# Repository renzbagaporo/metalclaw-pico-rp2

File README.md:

# MetalClaw Pico RP2

An RP2354B board for testing firmware on a Raspberry Pi Pico or Pico 2.
[Metalclaw firmware](https://github.com/renzbagaporo/metalclaw-fw) provides
Python-controlled peripheral emulation and a USB debug probe. The carrier
connects those functions to the target's GPIO, analogue inputs and SWD port.

- Emulate I2C, SPI and UART devices connected to the target.
- Generate and read digital signals on the target's exposed GPIOs.
- Supply filtered PWM stimulus to its three ADC inputs.
- Program and debug the target through SWD; control its reset and regulator enable.

## Hardware

| | |
| --- | --- |
| Controller | RP2354B with 2 MB in-package flash |
| PSRAM | 8 MB, APS6404L-3SQR-SN |
| USB | USB-C, full speed |
| Target interface | Pico / Pico 2 GPIO, power and SWD contacts; 3.3 V GPIO logic |
| Board | 21 × 51 mm, four layers, 1.6 mm, castellated edges |

## Pinout

The **Pico** columns name the target signals; the **RP2354B** columns show
the carrier GPIOs connected to them. The colored function labels belong to
the carrier. J2 programs the carrier; the three contacts at the bottom are
the target's SWD interface.

Several target pins have multiple carrier GPIO branches. Only one push-pull
carrier branch may drive a given target net at a time. GP26–GP28 pass through
permanent analogue filters and do not provide an unfiltered high-speed
digital path.

## Connections and controls

Connect the carrier to the PC through **J1 USB-C**. The target's own USB port remains
available for its application or console. To enter the carrier's USB
bootloader, hold BOOTSEL, press and release RESET, then release BOOTSEL.
Firmware build instructions and the Python API are in
[metalclaw-fw](https://github.com/renzbagaporo/metalclaw-fw).

### Power

The carrier USB supply feeds the target's VSYS through a Schottky diode.
VSYS also feeds the carrier's regulator, so powering the Pico through its
own USB port powers the carrier too. The two USB VBUS inputs are diode-isolated;
the carrier and target have separate 3.3 V regulators.

The target's `3V3_EN` control disables its regulator while leaving the
carrier powered. Before disabling it, firmware must release all target-facing
GPIO, PWM and SWD outputs and disable their pulls.

## Design files

Open [metalclaw-pico-rp2.kicad_pro](metalclaw-pico-rp2.kicad_pro) in KiCad 9.

- [Schematic](metalclaw-pico-rp2.kicad_sch)
- [PCB layout](metalclaw-pico-rp2.kicad_pcb)

Project-local footprints and models are in `footprints/` and `3dmodels/`.

## Manufacturing

Generate the Gerbers, assembly BOM and placement file with:

```sh
python3 tools/gen_fab.py
```

The files are written to `fab/`. Upload `metalclaw-pico-rp2_gerbers.zip` for
the PCB, and `BOM_jlcpcb.csv` / `CPL_jlcpcb.csv` for assembly. The Pico outline
footprint is part of the carrier PCB, not a module to populate.

Order files belong on [tagged releases](https://github.com/renzbagaporo/metalclaw-pico-rp2/releases).

## License

[CC BY-SA 4.0](LICENSE). See [NOTICE.md](NOTICE.md) for attribution and third-party terms.

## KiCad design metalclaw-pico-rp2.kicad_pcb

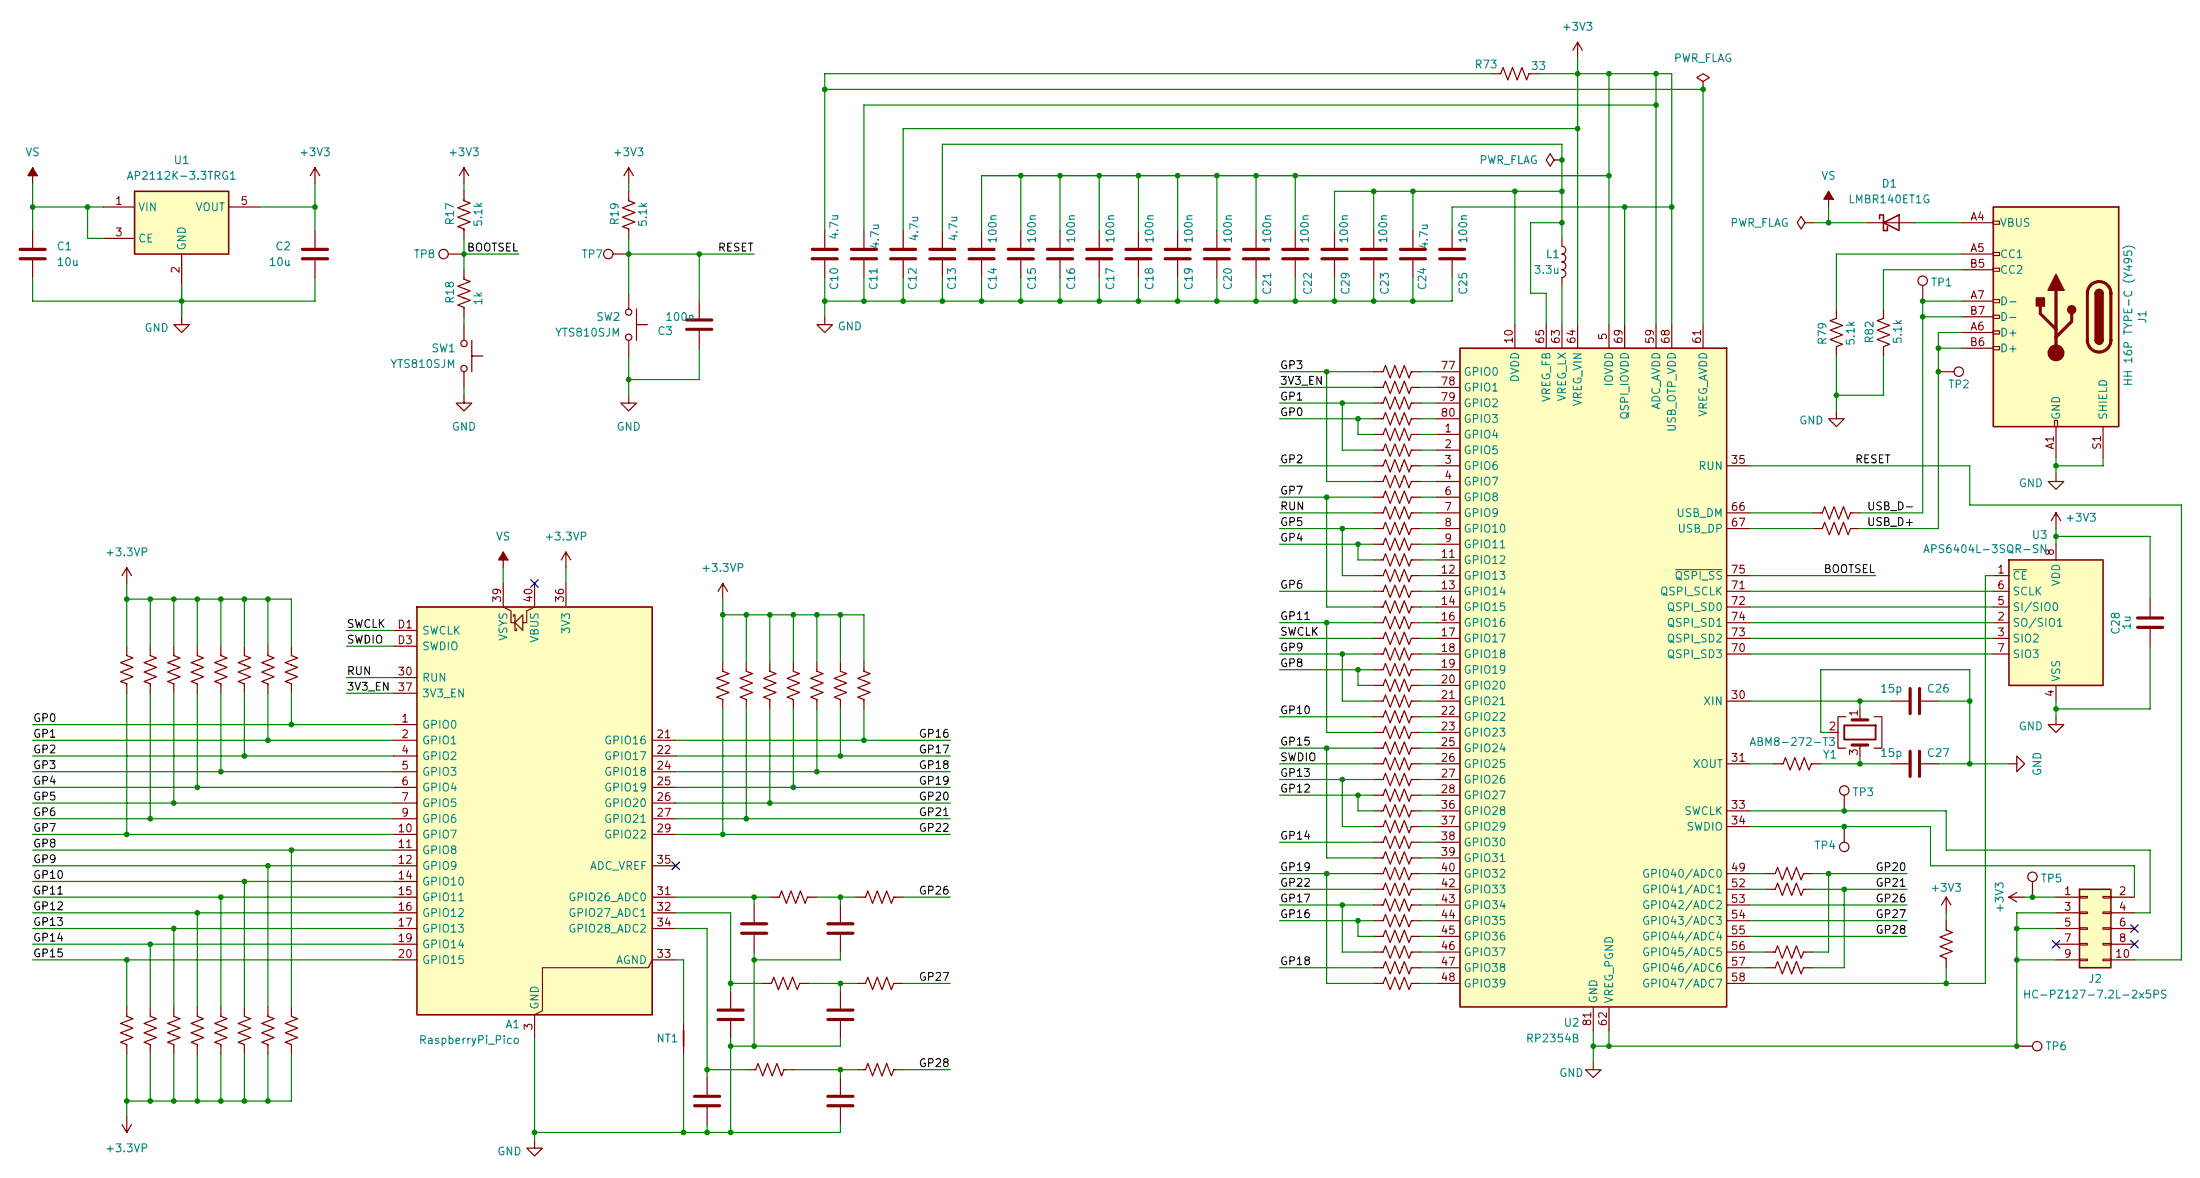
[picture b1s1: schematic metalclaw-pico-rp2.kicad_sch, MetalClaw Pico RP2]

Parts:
A1: RaspberryPi_Pico; RaspberryPi_Pico_SMD
C1, C2: 10u; C_0603_1608Metric; LCSC C19702
C3, C14, C15, C16, C17, C18, C19, C20, C21, C22, C23, C25, C29: 100n; C_0201_0603Metric; LCSC C190183
C4, C5, C6: 1.5n; C_0402_1005Metric; Mouser 81-GRM1555C1H152JA1D
C7, C8, C9: 10n; C_0201_0603Metric; Mouser 810-C0603X7R1A103K
C10, C11, C12, C13, C24: 4.7u; C_0402_1005Metric; MPN GRM155R60J475ME47D; LCSC C82453
C26, C27: 15p; C_0201_0603Metric; Mouser 81-GRM0335C1H150JA1D
C28: 1u; C_0402_1005Metric; LCSC C52923
D1: LMBR140ET1G; D_SOD-323HE_SS14HE; MPN LMBR140ET1G; LCSC C172430
J1: HH 16P TYPE-C (Y495); USB_C_Receptacle_HH_Y495_16P_TopMnt_Horizontal; MPN HH 16P TYPE-C (Y495); LCSC C52209111
J2: HC-PZ127-7.2L-2x5PS; HCTL_HC-PZ127-7.2L-2x5PS; MPN HC-PZ127-7.2L-2x5PS; LCSC C27985146
L1: 3.3u; L_Abracon_AOTA-B201610S3R3-101-T; Mouser 815-AB201610S3R3101T
NT1: NetTie_2; NetTie-2_SMD_Pad0.5mm
R1, R2, R3, R4, R5, R6, R7, R8, R9, R10, R11, R12, R13, R14, R15, R16, R17, R19, R20, R21, R22, R25, R27, R28, R29, R79, R82: 5.1k; R_0201_0603Metric; Mouser 603-RC0201FR-075K1L
R18, R34, R42, R78: 1k; R_0201_0603Metric; Mouser 603-RC0201FR-071KL
R23, R24, R26, R83: 2.2k; R_0201_0603Metric; Mouser 603-RC0201FR-072K2L
R30, R31, R32: 330; R_0201_0603Metric; Mouser 603-RC0201FR-07330RL
R33, R35, R36, R37, R38, R39, R40, R41, R43, R44, R45, R46, R47, R48, R49, R50, R51, R52, R53, R54, R55, R56, R57, R58, R59, R60, R61, R62, R63, R64, R65, R66, R67, R68, R69, R70, R71, R72, R74, R75, R76, R77: 100; R_0201_0603Metric; Mouser 603-RC0201FR-07100RL
R73: 33; R_0402_1005Metric; Mouser 603-RC0402FR-0733RL
R80, R81: 27; R_0201_0603Metric; MPN WR02X27R0FAL; LCSC C367568
SW1, SW2: YTS810SJM; SW_SPST_PTS810; MPN YTS810SJM; LCSC C2910643
TP1, TP2, TP3, TP4, TP5, TP6, TP7, TP8: TestPoint; TestPoint_Pad_D1.0mm
U1: AP2112K-3.3TRG1; SOT-23-5; MPN AP2112K-3.3TRG1; LCSC C51118
U2: RP2354B; QFN-80_RP2354B_10x10mm_P0.4mm_EP3.4mm_ViaAwarePaste; MPN SC1512(13)-A4; Mouser 358-SC151213
U3: APS6404L-3SQR-SN; SOIC-8_3.9x4.9mm_P1.27mm; MPN APS6404L-3SQR-SN; LCSC C5333729
Y1: ABM8-272-T3; Crystal_SMD_3225-4Pin_3.2x2.5mm; Mouser 815-ABM8-272-T3

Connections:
+3.3VP: A1.36 (3V3), R1.2, R2.1, R3.2, R4.1, R5.2, R6.1, R7.2, R8.1, R9.2, R10.1, R11.2, R12.1, R13.2, R14.1, R15.2, R16.1, R20.2, R21.2, R22.2, R25.2, R27.2, R28.2, R29.2
+3V3: C2.1, C11.2, C12.2, C14.2, C15.2, C16.2, C17.2, C18.2, C19.2, C20.2, C21.2, C22.2, C25.2, C28.1, J2.1, R17.1, R19.1, R73.1, R83.2, TP5.1, U1.5 (VOUT), U2.5 (IOVDD), U2.15 (IOVDD), U2.24 (IOVDD), U2.29 (IOVDD), U2.41 (IOVDD), U2.50 (IOVDD), U2.59 (ADC_AVDD), U2.60 (IOVDD), U2.64 (VREG_VIN), U2.68 (USB_OTP_VDD), U2.69 (QSPI_IOVDD), U2.76 (IOVDD), U3.8 (VDD)
/3V3_EN: A1.37 (3V3_EN), R34.1
/BOOTSEL: R17.2, R18.1, TP8.1, U2.75 (~QSPI_SS)
/GP0: A1.1 (GPIO0), R15.1, R36.1, R37.1
/GP1: A1.2 (GPIO1), R13.1, R35.1, R38.1
/GP2: A1.4 (GPIO2), R11.1, R39.1
/GP3: A1.5 (GPIO3), R9.1, R33.1, R40.1
/GP4: A1.6 (GPIO4), R7.1, R44.1, R45.1
/GP5: A1.7 (GPIO5), R5.1, R43.1, R46.1
/GP6: A1.9 (GPIO6), R3.1, R47.1
/GP7: A1.10 (GPIO7), R1.1, R41.1, R48.1
/GP8: A1.11 (GPIO8), R16.2, R52.1, R53.1
/GP9: A1.12 (GPIO9), R14.2, R51.1, R54.1
/GP10: A1.14 (GPIO10), R12.2, R55.1
/GP11: A1.15 (GPIO11), R10.2, R49.1, R56.1
/GP12: A1.16 (GPIO12), R8.2, R60.1, R61.1
/GP13: A1.17 (GPIO13), R6.2, R59.1, R62.1
/GP14: A1.19 (GPIO14), R4.2, R63.1
/GP15: A1.20 (GPIO15), R2.2, R57.1, R64.1
/GP16: A1.21 (GPIO16), R29.1, R68.1, R69.1
/GP17: A1.22 (GPIO17), R28.1, R67.1, R70.1
/GP18: A1.24 (GPIO18), R27.1, R71.1
/GP19: A1.25 (GPIO19), R25.1, R65.1, R72.1
/GP20: A1.26 (GPIO20), R22.1, R74.2, R76.2
/GP21: A1.27 (GPIO21), R21.1, R75.2, R77.2
/GP22: A1.29 (GPIO22), R20.1, R66.1
/GP26: R30.1, U2.53 (GPIO42/ADC2)
/GP27: R31.1, U2.54 (GPIO43/ADC3)
/GP28: R32.1, U2.55 (GPIO44/ADC4)
/RESET: C3.2, J2.10, R19.2, SW2.2, TP7.1, U2.35 (RUN)
/RUN: A1.30 (RUN), R42.1
/SWCLK: A1.D1 (SWCLK), R50.1
/SWDIO: A1.D3 (SWDIO), R58.1
/USB_D+: J1.A6 (D+), J1.B6 (D+), R81.1, TP2.1
/USB_D-: J1.A7 (D-), J1.B7 (D-), R80.1, TP1.1
GND: A1.3 (GND), A1.8 (GND), A1.13 (GND), A1.18 (GND), A1.23 (GND), A1.28 (GND), A1.38 (GND), A1.D2 (GND), C1.2, C2.2, C3.1, C4.1, C5.1, C6.1, C7.1, C8.1, C9.1, C10.1, C11.1, C12.1, C13.1, C14.1, C15.1, C16.1, C17.1, C18.1, C19.1, C20.1, C21.1, C22.1, C23.1, C24.1, C25.1, C26.2, C27.1, C28.2, C29.1, J1.A1 (GND), J1.A12 (GND), J1.B1 (GND), J1.B12 (GND), J1.S1 (SHIELD), J2.3, J2.5, J2.9, NT1.1, R79.1, R82.1, SW1.1, SW2.1, TP6.1, U1.2 (GND), U2.62 (VREG_PGND), U2.81 (GND), U3.4 (VSS), Y1.2 (G), Y1.4 (G)
unnamed: A1.33 (AGND), NT1.2
unnamed: A1.31 (GPIO26_ADC0), C6.2, R26.2
unnamed: A1.32 (GPIO27_ADC1), C5.2, R24.2
unnamed: A1.34 (GPIO28_ADC2), C4.2, R23.2
unnamed: C7.2, R26.1, R30.2
unnamed: C8.2, R24.1, R31.2
unnamed: C9.2, R23.1, R32.2
unnamed: C27.2, R78.2, Y1.3
unnamed: D1.2 (A), J1.A4 (VBUS), J1.A9 (VBUS), J1.B4 (VBUS), J1.B9 (VBUS)
unnamed: J1.A5 (CC1), R79.2
unnamed: J1.B5 (CC2), R82.2
unnamed: J2.2, TP4.1, U2.34 (SWDIO)
unnamed: J2.4, TP3.1, U2.33 (SWCLK)
unnamed: R18.2, SW1.2
unnamed: R33.2, U2.77 (GPIO0)
unnamed: R34.2, U2.78 (GPIO1)
unnamed: R35.2, U2.79 (GPIO2)
unnamed: R36.2, U2.80 (GPIO3)
unnamed: R37.2, U2.1 (GPIO4)
unnamed: R38.2, U2.2 (GPIO5)
unnamed: R39.2, U2.3 (GPIO6)
unnamed: R40.2, U2.4 (GPIO7)
unnamed: R41.2, U2.6 (GPIO8)
unnamed: R42.2, U2.7 (GPIO9)
unnamed: R43.2, U2.8 (GPIO10)
unnamed: R44.2, U2.9 (GPIO11)
unnamed: R45.2, U2.11 (GPIO12)
unnamed: R46.2, U2.12 (GPIO13)
unnamed: R47.2, U2.13 (GPIO14)
unnamed: R48.2, U2.14 (GPIO15)
unnamed: R49.2, U2.16 (GPIO16)
unnamed: R50.2, U2.17 (GPIO17)
unnamed: R51.2, U2.18 (GPIO18)
unnamed: R52.2, U2.19 (GPIO19)
unnamed: R53.2, U2.20 (GPIO20)
unnamed: R54.2, U2.21 (GPIO21)
unnamed: R55.2, U2.22 (GPIO22)
unnamed: R56.2, U2.23 (GPIO23)
unnamed: R57.2, U2.25 (GPIO24)
unnamed: R58.2, U2.26 (GPIO25)
unnamed: R59.2, U2.27 (GPIO26)
unnamed: R60.2, U2.28 (GPIO27)
unnamed: R61.2, U2.36 (GPIO28)
unnamed: R62.2, U2.37 (GPIO29)
unnamed: R63.2, U2.38 (GPIO30)
unnamed: R64.2, U2.39 (GPIO31)
unnamed: R65.2, U2.40 (GPIO32)
unnamed: R66.2, U2.42 (GPIO33)
unnamed: R67.2, U2.43 (GPIO34)
unnamed: R68.2, U2.44 (GPIO35)
unnamed: R69.2, U2.45 (GPIO36)
unnamed: R70.2, U2.46 (GPIO37)
unnamed: R71.2, U2.47 (GPIO38)
unnamed: R72.2, U2.48 (GPIO39)
unnamed: R74.1, U2.49 (GPIO40/ADC0)
unnamed: R75.1, U2.52 (GPIO41/ADC1)
unnamed: R76.1, U2.56 (GPIO45/ADC5)
unnamed: R77.1, U2.57 (GPIO46/ADC6)
unnamed: R83.1, U2.58 (GPIO47/ADC7), U3.1 (~CE)
unnamed: U2.71 (QSPI_SCLK), U3.6 (SCLK)
unnamed: U2.72 (QSPI_SD0), U3.5 (SI/SIO0)
unnamed: U2.74 (QSPI_SD1), U3.2 (SO/SIO1)
unnamed: U2.73 (QSPI_SD2), U3.3 (SIO2)
unnamed: U2.70 (QSPI_SD3), U3.7 (SIO3)
unnamed: R80.2, U2.66 (USB_DM)
unnamed: R81.2, U2.67 (USB_DP)
unnamed: C10.2, R73.2, U2.61 (VREG_AVDD)
unnamed: C13.2, C23.2, C24.2, C29.2, L1.1, U2.10 (DVDD), U2.32 (DVDD), U2.51 (DVDD), U2.65 (VREG_FB)
unnamed: L1.2, U2.63 (VREG_LX)
unnamed: C26.1, U2.30 (XIN), Y1.1
unnamed: R78.1, U2.31 (XOUT)
VS: A1.39 (VSYS), C1.1, D1.1 (K), U1.1 (VIN), U1.3 (CE)

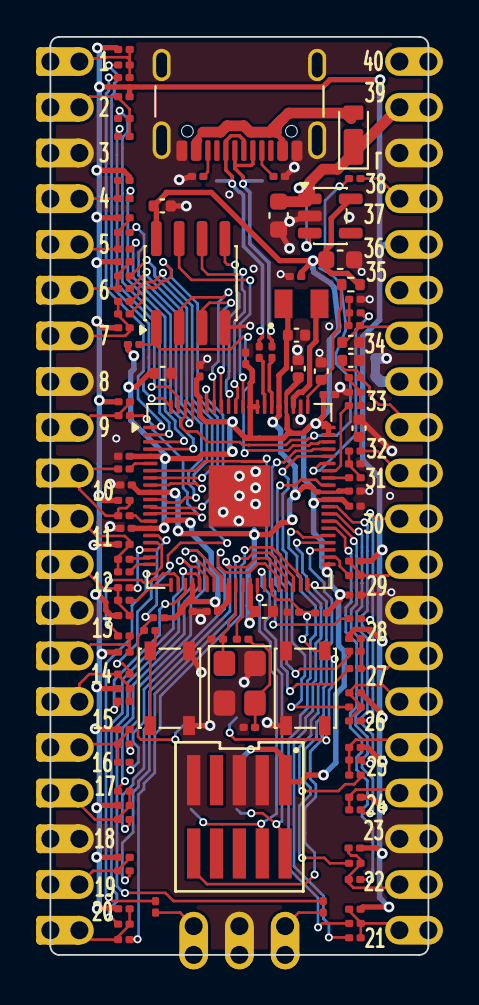
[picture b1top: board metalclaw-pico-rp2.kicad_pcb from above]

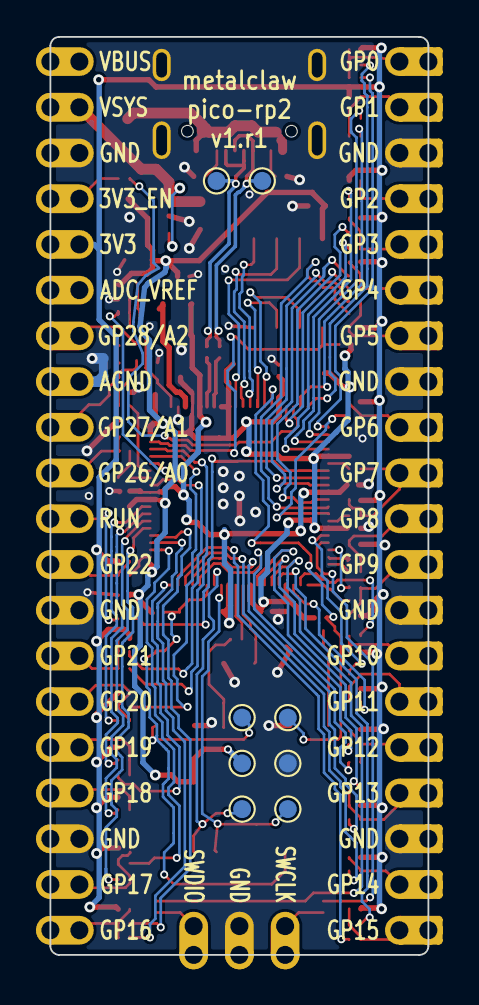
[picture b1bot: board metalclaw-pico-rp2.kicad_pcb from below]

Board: 4 copper layers, 21.0 x 51.0 mm, 132 parts (9 on the bottom side), 109 nets.

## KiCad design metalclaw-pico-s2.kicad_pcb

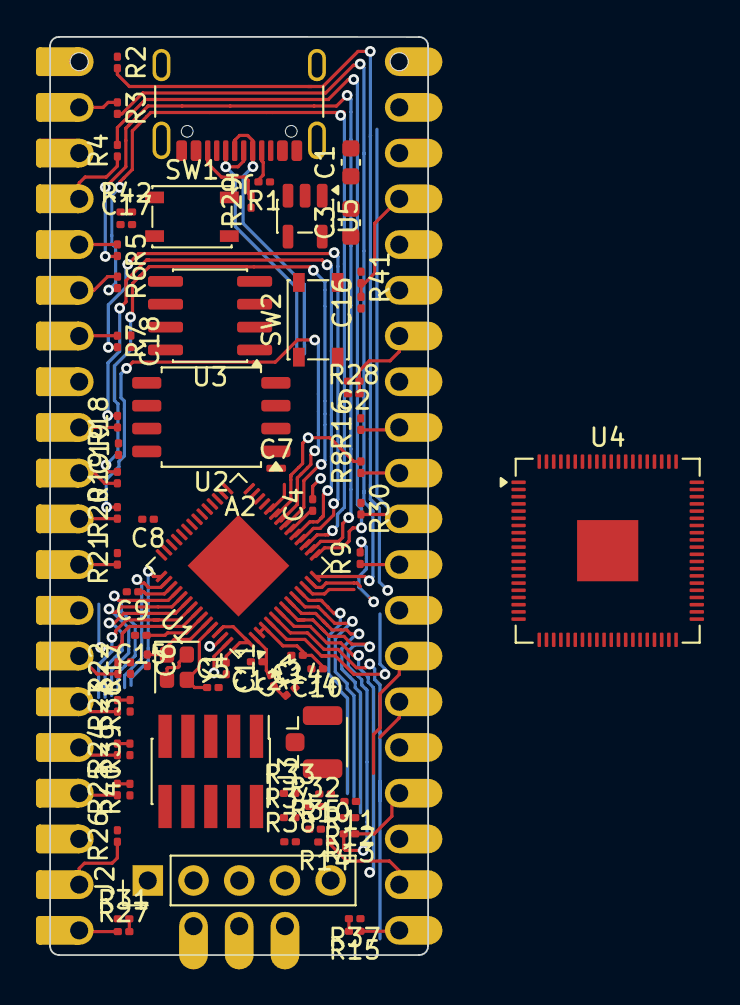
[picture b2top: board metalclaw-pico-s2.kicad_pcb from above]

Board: 4 copper layers, 21.0 x 51.0 mm, 75 parts (0 on the bottom side), 84 nets.

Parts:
A2: RaspberryPi_Pico; RaspberryPi_Pico_SMD
C1, C3: 10u; C_0603_1608Metric
C2, C10, C11, C16, C17, C18, C19: 1u; C_0201_0603Metric
C4, C7, C8, C9, C14, C15: 100n; C_0201_0603Metric
C5, C6: 6p; C_0201_0603Metric
C12, C13: C; C_0201_0603Metric
J1: USB_C_Receptacle_USB2.0_14P; USB_C_Receptacle_GCT_USB4105-xx-A_16P_TopMnt_Horizontal
J2: Conn_01x05; PinHeader_1x05_P2.54mm_Vertical
J3: Conn_02x05_Odd_Even; PinHeader_2x05_P1.27mm_Vertical_SMD
J4: Conn_Coaxial; U.FL_Hirose_U.FL-R-SMT-1_Vertical
L1: L; L_0201_0603Metric
R1, R17, R29, R30, R31, R32, R33, R34, R35, R36, R37, R38, R39, R40, R41, R42: 5.1k; R_0201_0603Metric
R2, R3, R4, R5, R6, R7, R8, R9, R10, R11, R12, R13, R14, R15, R16, R18, R19, R20, R21, R22, R23, R24, R25, R26, R27, R28: 220; R_0201_0603Metric
SW1, SW2: SW_Push; SW_SPST_PTS810
U1: ESP32-S2; QFN-56-1EP_7x7mm_P0.4mm_EP4x4mm
U2: MX25L3236FM2I-08G-TR; SOIC-8_5.3x5.3mm_P1.27mm
U3: APS6404L-3SQRx-SN; SOIC-8_3.9x4.9mm_P1.27mm
U4: RP2350B; QFN-80-1EP_10x10mm_P0.4mm_EP3.4x3.4mm
U5: XC6220B331MR; SOT-23-5
Y1: XRCGB40M000F1S2FR0; Crystal_SMD_2016-4Pin_2.0x1.6mm

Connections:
+3V3: A2.35 (ADC_VREF), C3.1, C4.1, C7.1, C8.1, C9.1, C10.1, C11.1, C14.1, C15.1, J3.1, R17.1, R32.1, R33.1, R34.1, R35.1, R36.1, R37.1, R38.1, R39.1, R40.1, R41.1, R42.1, U1.1 (VDDA), U1.3 (VDD3P3), U1.4 (VDD3P3), U1.20 (VDD3P3_RTC), U1.27 (VDD3P3_RTC_IO), U1.45 (VDD3P3_CPU), U1.51 (VDDA), U1.54 (VDDA), U5.5 (VOUT)
/3V3_EN: A2.37 (3V3_EN), C16.2, R41.2, U1.5 (GPIO0)
/GP0: R2.2, U1.13 (GPIO8)
/GP1: R3.2, U1.14 (GPIO9)
/GP2: R4.2, U1.15 (GPIO10)
/GP3: R5.2, U1.16 (GPIO11)
/GP4: R6.2, U1.17 (GPIO12)
/GP5: R7.2, U1.18 (GPIO13)
/GP6: R18.2, U1.19 (GPIO14)
/GP7: R19.2, U1.21 (XTAL_32K_P)
/GP8: R20.2, U1.22 (XTAL_32K_N)
/GP9: R21.2, U1.37 (GPIO33)
/GP10: R17.2, R22.2, U1.38 (GPIO34)
/GP11: R23.2, R36.2, U1.39 (GPIO35)
/GP12: R24.2, R39.2, U1.40 (GPIO36)
/GP13: R25.2, R40.2, U1.42 (GPIO38)
/GP14: R26.2, U1.41 (GPIO37)
/GP15: R27.2, R31.2, U1.55 (GPIO46)
/GP16: R15.2, R37.2, U1.6 (GPIO1)
/GP17: R14.2, R38.2, U1.7 (GPIO2)
/GP18: R13.2, R35.2, U1.8 (GPIO3)
/GP19: R12.2, R34.2, U1.9 (GPIO4)
/GP20: R11.2, R32.2, U1.10 (GPIO5)
/GP21: R10.2, R33.2, U1.11 (GPIO6)
/GP22: R9.2, U1.12 (GPIO7)
/GP26: R8.2, U1.23 (DAC_1)
/GP27: R16.2, U1.24 (DAC_2)
/GP28: A2.34 (GPIO28_ADC2), C2.1, R28.2
/MTCK: J2.2, J3.4, U1.43 (MTCK)
/MTDI: J2.4, J3.8, U1.46 (MDTI)
/MTDO: J2.3, J3.6, U1.44 (MTD0)
/MTMS: J2.1, J3.2, U1.47 (MTMS)
/RESET: C17.2, J2.5, R42.2, U1.56 (CHIP_PU)
/RUN: A2.30 (RUN), R30.2, U1.50 (GPIO45)
/SWCLK: A2.D1 (SWCLK), U1.48 (U0TXD)
/SWDIO: A2.D3 (SWDIO), U1.49 (U0RXD)
/USB_D+: J1.A6 (D+), J1.B6 (D+), U1.26 (GPIO20/USB_D+)
/USB_D-: J1.A7 (D-), J1.B7 (D-), U1.25 (GPIO19/USB_D-)
GND: A2.3 (GND), A2.8 (GND), A2.13 (GND), A2.18 (GND), A2.23 (GND), A2.28 (GND), A2.33 (AGND), A2.38 (GND), A2.D2 (GND), C1.2, C2.2, C3.2, C4.2, C5.2, C6.2, C7.2, C8.2, C9.2, C10.2, C11.2, C12.2, C13.2, C14.2, C15.2, C18.1, C19.2, J1.A1 (GND), J1.A12 (GND), J1.B1 (GND), J1.B12 (GND), J3.3, J3.5, J3.7, J3.9, J4.2 (Ext), R1.1, R29.1, R30.1, R31.1, SW1.1, SW2.1, U1.57 (GND), U2.4 (GND), U3.4 (VSS), U5.2 (GND), Y1.2 (G), Y1.4 (G)
unnamed: A2.1 (GPIO0), R2.1
unnamed: A2.2 (GPIO1), R3.1
unnamed: A2.4 (GPIO2), R4.1
unnamed: A2.5 (GPIO3), R5.1
unnamed: A2.6 (GPIO4), R6.1
unnamed: A2.7 (GPIO5), R7.1
unnamed: A2.9 (GPIO6), R18.1
unnamed: A2.10 (GPIO7), R19.1
unnamed: A2.11 (GPIO8), R20.1
unnamed: A2.12 (GPIO9), R21.1
unnamed: A2.14 (GPIO10), R22.1
unnamed: A2.15 (GPIO11), R23.1
unnamed: A2.16 (GPIO12), R24.1
unnamed: A2.17 (GPIO13), R25.1
unnamed: A2.19 (GPIO14), R26.1
unnamed: A2.20 (GPIO15), R27.1
unnamed: A2.21 (GPIO16), R15.1
unnamed: A2.22 (GPIO17), R14.1
unnamed: A2.24 (GPIO18), R13.1
unnamed: A2.25 (GPIO19), R12.1
unnamed: A2.26 (GPIO20), R11.1
unnamed: A2.27 (GPIO21), R10.1
unnamed: A2.29 (GPIO22), R9.1
unnamed: A2.31 (GPIO26_ADC0), R8.1
unnamed: A2.32 (GPIO27_ADC1), R16.1
unnamed: C16.1, SW2.2
unnamed: C17.1, SW1.2
unnamed: J1.A5 (CC1), R1.2
unnamed: J1.B5 (CC2), R29.2
unnamed: C13.1, J4.1 (In), L1.2
unnamed: R28.1, U1.28 (GPIO21)
unnamed: C12.1, L1.1, U1.2 (LNA_IN)
unnamed: U1.34 (SPICLK), U2.6 (SCLK), U3.6 (SCLK)
unnamed: U1.33 (SPICS0), U2.1 (~CS)
unnamed: U1.29 (SPICS1), U3.1 (~CE)
unnamed: U1.36 (SPID), U2.5 (SI/SIO0), U3.5 (SI/SIO0)
unnamed: U1.31 (SPIHD), U2.7 (~HOLD/SIO3), U3.7 (SIO3)
unnamed: U1.35 (SPIQ), U2.2 (SO/SIO1), U3.2 (SO/SIO1)
unnamed: U1.32 (SPIWP), U2.3 (~WP/SIO2), U3.3 (SIO2)
unnamed: C6.1, U1.52 (XTAL_N), Y1.1
unnamed: C5.1, U1.53 (XTAL_P), Y1.3
unnamed: U4.10 (DVDD), U4.32 (DVDD), U4.51 (DVDD)
unnamed: U4.5 (IOVDD), U4.15 (IOVDD), U4.24 (IOVDD), U4.29 (IOVDD), U4.41 (IOVDD), U4.50 (IOVDD), U4.60 (IOVDD), U4.76 (IOVDD)
VBUS: A2.40 (VBUS), C1.1, J1.A4 (VBUS), J1.A9 (VBUS), J1.B4 (VBUS), J1.B9 (VBUS), U5.1 (VIN), U5.3 (CE)
VDD: C18.2, C19.1, U1.30 (VDD_SPI), U2.8 (VCC), U3.8 (VDD)
